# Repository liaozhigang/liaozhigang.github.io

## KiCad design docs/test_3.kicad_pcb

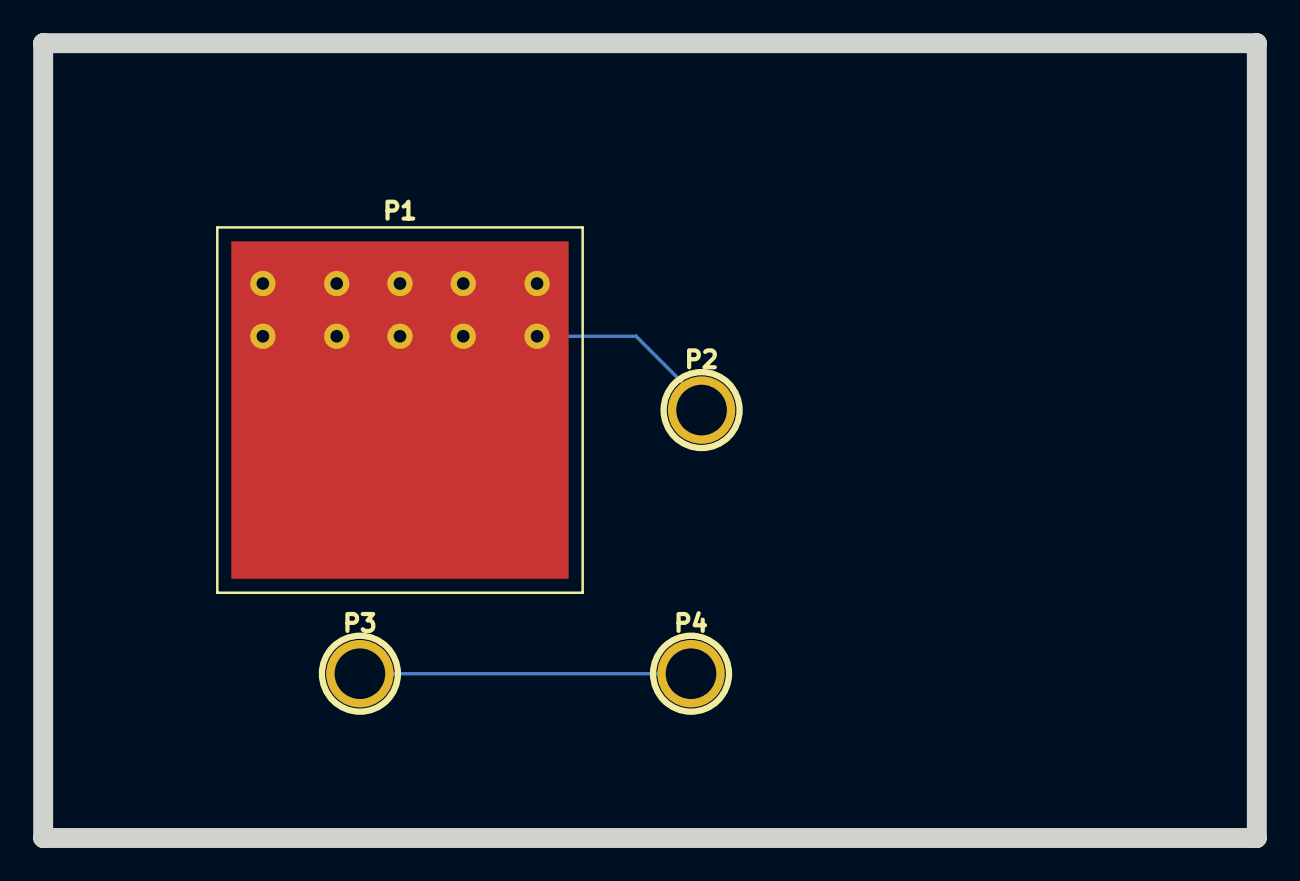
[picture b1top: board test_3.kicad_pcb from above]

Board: 2 copper layers, 73.1 x 47.9 mm, 4 parts (0 on the bottom side), 2 nets.

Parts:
P1: CONN_1; 1pin_thermal
P2, P3, P4: CONN_1; 1pin

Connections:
/NET1: P3.1, P4.1
/NET2: P1.1, P2.1

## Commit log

2019-11-14 test flutter web
2019-11-19 make video player work on web
2019-11-25 temp checkin
2019-11-25 actions, messages
2019-12-26 add font family
2020-01-07 change to only designer
2020-02-26 add a.json
2020-08-17 map designer
2020-08-18 map progress
2020-08-21 progress
2023-11-01 To test flutter_pcb
2023-11-01 remove some unused files
2023-11-01 Add testing project for the static web server
2023-11-02 add passcode for web mode
2023-11-07 add command window
2023-11-09 refine command window
2024-05-25 new model and command system
